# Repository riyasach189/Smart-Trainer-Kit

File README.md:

## Background and Motivation:
- The Digital Trainer Kit serves as a vital tool for facilitating learning, teaching, and testing of digital electronic circuits.
- It plays a crucial role in the laboratory component of the Digital Circuits course offered in Semester 1 at IIIT-D.
- However, the current trainer kits deployed in the ECE labs suffer from drawbacks such as being bulky, expensive, and featuring redundant functions.

## Objectives:
- To find alternatives that are compact, lightweight, and reasonably priced, without compromising essential functionalities.
- To enhance the versatility and functionality of the proposed alternative, a microcontroller will be incorporated into the design. This addition will provide opportunities for future expansion and the inclusion of advanced features, empowering students to explore more complex digital circuits.

## Version 1
**BoM:**
```markdown
| Component                                     | Quantity | Price | Total Cost |
|-----------------------------------------------|----------|-------|------------|
| Arduino Board                                 | 1        | 550   | 550        |
| LEDs                                          | 22       | 0.8   | 17.6       |
| Resistors (330 Ohm)                           | 25       | 0.4   | 10         |
| Push Button Square Switch Self-Locking DPDT   | 10       | 5     | 50         |
| 4511 IC                                       | 1        | 21    | 21         |
| 7 Segment Display (Common Cathode)            | 1        | 7     | 7          |
| Passive Buzzer                                | 1        | 10    | 10         |
| 741 IC                                        | 1        | 9     | 9          |
| 4 mm Banana Sockets                           | 30       | 14.5  | 435        |
|                                               |          |       | 1109.6     |
```

**Features and Description:**
- A 12 V adapter powers the circuit. The Arduino has an inbuilt 12 V to 5 V converter. For the rest of the circuit, a Buck-Boost Converter is used.
- Nested 'for loops' are programmed in the Arduino to provide continuous clock signals of 3 frequencies - 0.1 Hz, 1 Hz, 10 Hz.
- The Continuity Checker can be used to debug faulty connections in a circuit.
- The Voltage Detector returns a HIGH value (LED turns on) when the voltage at a given point exceeds 2.5 V (to accommodate both the CMOS and TTL logic levels) in reference to the circuit ground, and returns a LOW value otherwise. A voltage divider is used between 5 V and GND to set the benchmark voltage at 2.5 V.
- The 4511 IC is connected to a 7-segment display to convert binary input to decimal digits (0 to 9).
- The Input LEDs can be operated using the Push Button switches connected to them.
- There are designated signal detector pins on the Arduino, which can be used to plot the clock signals on the Serial Plotter.

**Problems Encountered:**
- TinkerCad is not a reliable tool for large circuits; not recommended. They have also removed many components from their library.
- Initially, we planned to keep the clock frequencies variable, but Arduino can only run one infinite loop at a time. So, we decided to use nested 'for loops' to provide clock signals.
- We were trying to use a Common Cathode 7 segment display with a 7447 IC before we realized that that IC drives Common Anode displays.
- We found the 7805 IC unstable for voltage conversion, so we switched to a Buck-Boost Converter.
- When we kept the circuit on for a long time, the Input LEDs started flickering when switched ON. This issue remains unresolved. Possible reasons are:
  - The 12 V adapter could not meet the power requirements.
  - Arduino could not meet the power requirements.
  - The plastic and metal holes in the breadboard did not align, leading to loose connections.
  - Poor soldering on Buck-Boost Converter.
- We planned to use toggle switches in the circuit, but they were panel mount instead of PCB mount. So we switched to push button switches.

**Resources:**
- KiCad - PCB Design
- [7 Segment Display with 4511 IC](https://youtu.be/KZTwr95eINc)
- [Arduino for Beginners](https://youtu.be/d8_xXNcGYgo)
- [How to Use DPDT Switches](https://youtu.be/f0EMblUCp54)

## Version 2
**BoM:**
```markdown
| Component                                | Quantity | Price | Total Cost |
|------------------------------------------|----------|-------|------------|
| RPi Pico Board                           | 1        | 345   | 345        |
| LEDs                                     | 18       | 0.8   | 14.4       |
| Resistors (330 Ohm)                      | 24       | 0.4   | 9.6        |
| Toggle switches                          | 10       | 20    | 200        |
| 4511 IC                                  | 1        | 21    | 21         |
| 7 Segment Display (Common Cathode)       | 1        | 7     | 7          |
| DIP Socket (16 Pin)                      | 1        | 3     | 3          |
| ZIF Socket (16 Pin)                      | 1        | 50    | 50         |
| Passive Buzzer                           | 1        | 10    | 10         |
| 2 mm Banana Sockets                      | 30       | 26    | 780        |
| Rotary Encoder                           | 1        | 50    | 50         |
| LCD (16 x 2) + I2C                       | 1        | 188   | 188        |
| 18 mm Standoffs                          | 4        | 16    | 64         |
| Potentiometer                            | 1        | 6     | 6          |
| Female Headers                           | 44       | 1.125 | 49.5       |
|                                          |          |       | 1797.5     |
```

**Features and Description:**
- A 5 V power supply powers the circuit.
- State machines on the rp2040 to provide continuous clock signals of 3 frequencies - 1 Hz, 5 Hz, 10 Hz.
- The Continuity Checker can be used to debug a circuit.
- The 4511 IC is connected to a 7-segment display to convert binary input to decimal digits (0 to 9).
- The Input LEDs can be operated using the toggle switches connected to them.
- The rotary menu is displayed on the LCD screen and operated using the rotary encoder. It has 2 options: IC Tester and Voltmeter.
- If 'Voltmeter' is selected, the LCD displays the voltage (in reference to the circuit GND) at the given point. To exit the voltmeter mode, click on the rotary encoder button.
- To use the IC Tester, plug the IC into the DIP socket (If it's a 14 Pin IC, leave the last 2 pins of the DIP Socket empty, i.e., start from the beginning of the DIP Socket). Then, select which IC you wish to test. The LCD will display '[ ]' for every gate that is functioning and '[!]' for every gate that is not functioning in the IC (keeping the IC notch on the left).

**Problems Encountered:**
- RPi Pico should connect to a Windows system in theory, but we were only able to establish connection in Linux systems.
- To connect an RPi Pico, we require a microUSB to USB cable which supports data and charge transfer, not just charge transfer.
- Pico's LED light did not turn ON the moment it was connected to the power supply, which led us to believe that the Pico was faulty (which is not true).
- It took us some time to decide between using a raw rotary encoder or one mounted on a PCB, due to differences in available online resources. We settled on a PCB-mounted encoder but re-soldered its header pins to be more breadboard-friendly.
- We decided to use an I2C to connect the LCD screen to reduce the number of pins required on RPi Pico. This left extra pins for IC Tester and future expansion.
- RPi Pico is a dual-core processor in theory, but we were unable to use its multithreading functionality. We spent a long time trying to generate clock signals from Pico on the second thread, but Pico could only process one thread at a time. We finally decided to use 555 timers to generate clock signals.
- For the voltmeter, we wanted a range of (0, 5) V but the analog read pins of RPi Pico can take a maximum input of 3.3 V. So we used a voltage divider to map the range (0, 5) V onto (0, 3.3) V, then mapped that back to (0, 5) V in the code.
- We were later able to implement a clock without the use of separate threads through state machines on three different pins; however, having a variable clock was still not possible, and we settled on having three constant clock signals.
- We replaced push button switches with toggle switches because they were shorting the GND and VCC plane in the ON configuration. We believe push button switches are available in 2 different pinouts, but they look the same on the outside, ie. it is not possible to tell from the outside which type of push button switch it is. Also, toggle switches offer more tactile feedback and are a better choice.
- The biggest bottleneck in the whole design process was finding a PCB manufacturer.
- We realised we had missed some traces in the PCB when we assembled the first prototype, so we added them later.
- We had missed the Vcc and GND connection of the 4511 IC, and for some reason, it was causing the IC to heat up whenever we turned the RPi Pico on. This problem was resolved when we provided Vcc and GND to the IC.

**Resources:**
- [Rotary Encoder with RPi Pico](https://youtu.be/sgnEUxeNxpM)
- [RPi Pico for Beginners](https://youtu.be/1WDagiA8fdU)
- [Connect LCD to RPi Pico using I2C](https://www.tomshardware.com/how-to/lcd-display-raspberry-pi-pico)
- [555 Timer IC in Astable Mode](https://youtu.be/iJYm_BGqa1A)
- [555 Timer Frequency Calculator in Astable Mode](https://ohmslawcalculator.com/555-astable-calculator)
- [State Machines on RPi Pico](https://www.ourpcb.com/programmable-io.html)
  
## Contributors:
- Dr. Rahul Gupta - Manager, Research Labs (Supervisor of the Project)
- [Riya Sachdeva - EVE, BTech 2026](https://github.com/riyasach189)
- [Surat Sathi Samanta - EVE, BTech 2026](https://github.com/kio42069/)
- [Aarav Mathur - CSSS, BTech 2026](https://github.com/13100d/)

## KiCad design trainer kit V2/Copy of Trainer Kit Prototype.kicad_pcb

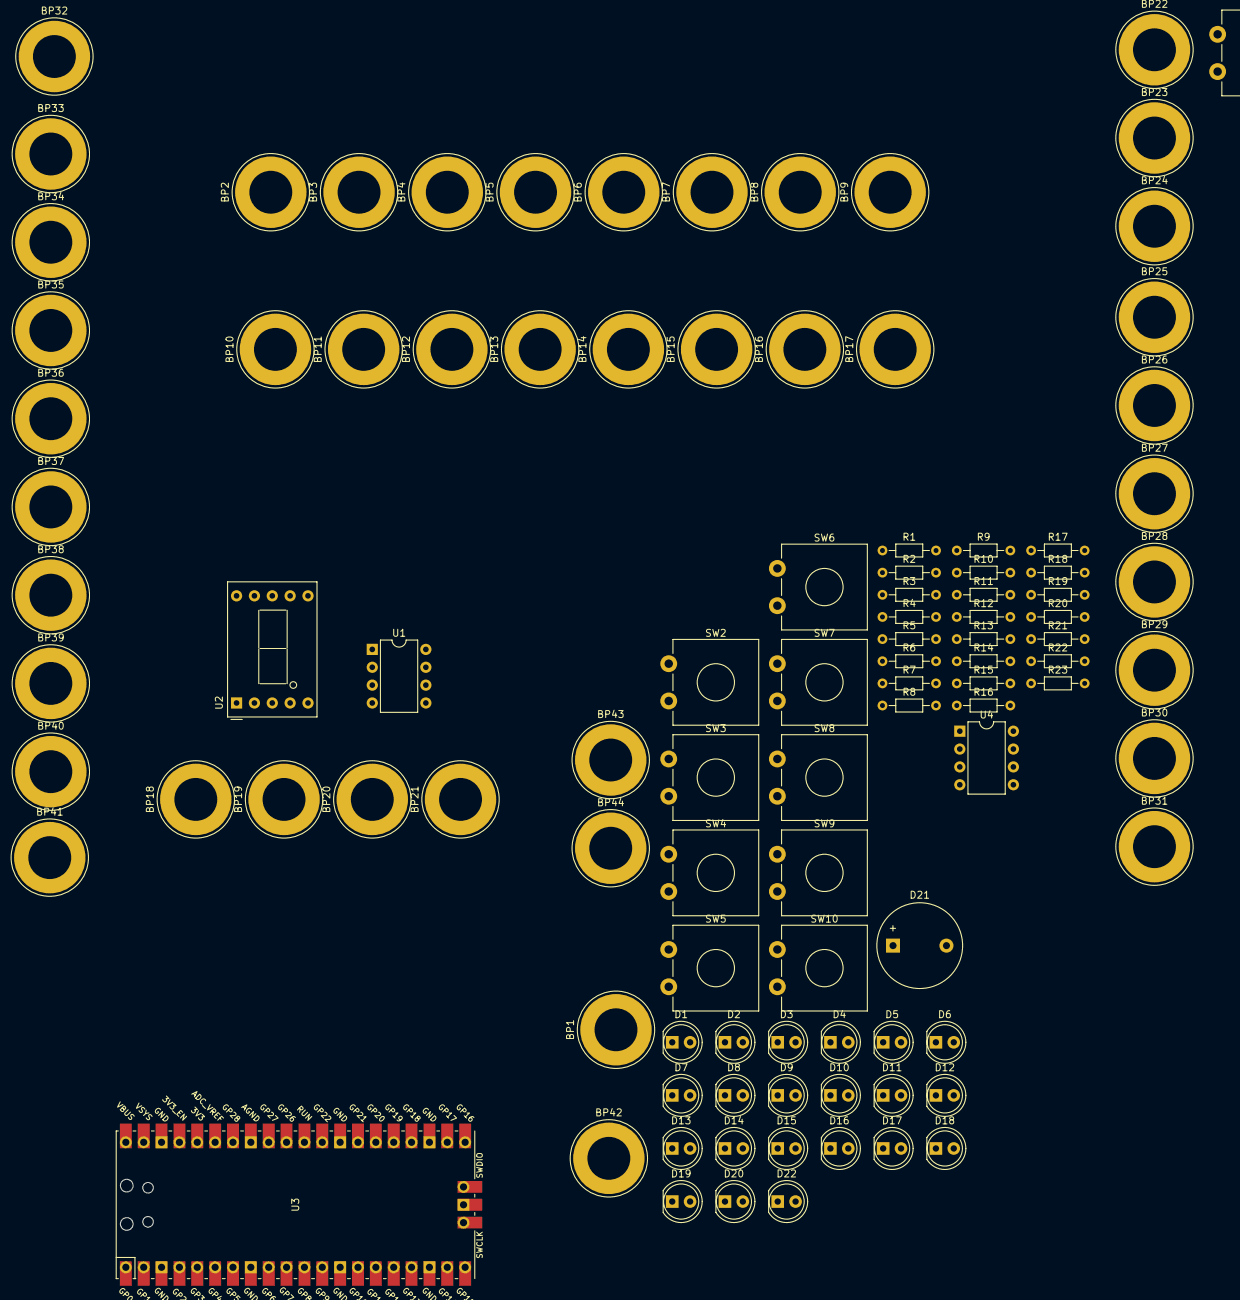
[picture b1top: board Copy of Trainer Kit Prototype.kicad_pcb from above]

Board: 2 copper layers, 103 parts (0 on the bottom side), 69 nets, no tracks yet.

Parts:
BP1, BP2, BP3, BP4, BP5, BP6, BP7, BP8, BP9, BP10, BP11, BP12, BP13, BP14, BP15, BP16, BP17, BP18, BP19, BP20, BP21, BP22, BP23, BP24, BP25, BP26, BP27, BP28, BP29, BP30, BP31, BP32, BP33, BP34, BP35, BP36, BP37, BP38, BP39, BP40, BP41, BP42, BP43, BP44: banana plug; Banana_Jack_1Pin
D1, D2, D3, D4, D5, D6, D7, D8, D9, D10, D11, D12, D13, D14, D15, D16, D17, D18, D19, D20: CQY99; LED_D5.0mm_IRGrey
D21: LED; Buzzer_12x9.5RM7.6
D22: LED; LED_D5.0mm_IRGrey
R1, R2, R3, R4, R5, R6, R7, R8, R9, R10, R11, R12, R13, R14, R15, R16, R17, R18, R19, R20, R21, R22, R23: 330; R_Axial_DIN0204_L3.6mm_D1.6mm_P7.62mm_Horizontal
SW1, SW2, SW3, SW4, SW5, SW6, SW7, SW8, SW9, SW10: SW_DIP_x01; SW_CW_GPTS203211B
U1: CD4511B; DIP-8_W7.62mm
U2: D168K; D1X8K
U3: Pico; RPi_Pico_SMD_TH
U4: LM741; DIP-8_W7.62mm

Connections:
+5V: BP44.1 (A), R23.2, SW1.1, SW2.1, SW3.1, SW4.1, SW5.1, SW6.1, SW7.1, SW8.1, SW9.1, SW10.1, U4.7 (V+)
/V(input): BP42.1 (A), U4.3 (+)
/Voltmeter Input Line: BP1.1 (A), U3.4 (GPIO2)
/automated testing (output lines): BP14.1 (A), U3.25 (GPIO19)
GNDREF: D21.2 (A), R1.1, R2.1, R3.1, R4.1, R5.1, R6.1, R7.1, R8.1, R9.1, R10.1, R11.1, R12.1, R13.1, R14.1, R15.1, R16.1, R17.1, R18.1, R19.1, R20.1, R21.1, R22.1, U1.5 (~EL), U2.3 (CC), U2.8 (CC), U3.8 (GND), U4.4 (V-)
unnamed: BP2.1 (A), U3.11 (GPIO8)
unnamed: BP3.1 (A), U3.12 (GPIO9)
unnamed: BP4.1 (A), U3.14 (GPIO10)
unnamed: BP5.1 (A), U3.15 (GPIO11)
unnamed: BP6.1 (A), U3.16 (GPIO12)
unnamed: BP7.1 (A), U3.17 (GPIO13)
unnamed: BP8.1 (A), U3.19 (GPIO14)
unnamed: BP9.1 (A), U3.20 (GPIO15)
unnamed: BP10.1 (A), U3.31 (GPIO26_ADC0)
unnamed: BP11.1 (A), U3.29 (GPIO22)
unnamed: BP12.1 (A), U3.27 (GPIO21)
unnamed: BP13.1 (A), U3.26 (GPIO20)
unnamed: BP15.1 (A), U3.24 (GPIO18)
unnamed: BP16.1 (A), U3.22 (GPIO17)
unnamed: BP17.1 (A), U3.21 (GPIO16)
unnamed: BP18.1 (A), U1.7 (DA)
unnamed: BP19.1 (A), U1.1 (DB)
unnamed: BP20.1 (A), U1.2 (DC)
unnamed: BP21.1 (A), U1.6 (DD)
unnamed: BP22.1 (A), D11.2 (A)
unnamed: BP23.1 (A), D12.2 (A)
unnamed: BP24.1 (A), D13.2 (A)
unnamed: BP25.1 (A), D14.2 (A)
unnamed: BP26.1 (A), D15.2 (A)
unnamed: BP27.1 (A), D16.2 (A)
unnamed: BP28.1 (A), D17.2 (A)
unnamed: BP29.1 (A), D18.2 (A)
unnamed: BP30.1 (A), D19.2 (A)
unnamed: BP31.1 (A), D20.2 (A)
unnamed: BP32.1 (A), D1.2 (A), SW9.2
unnamed: BP33.1 (A), D2.2 (A), SW8.2
unnamed: BP34.1 (A), D3.2 (A), SW7.2
unnamed: BP35.1 (A), D4.2 (A), SW1.2
unnamed: BP36.1 (A), D5.2 (A), SW2.2
unnamed: BP37.1 (A), D6.2 (A), SW3.2
unnamed: BP38.1 (A), D7.2 (A), SW4.2
unnamed: BP39.1 (A), D8.2 (A), SW5.2
unnamed: BP40.1 (A), D9.2 (A), SW6.2
unnamed: BP41.1 (A), D10.2 (A), SW10.2
unnamed: BP43.1 (A), D21.1 (K)
unnamed: D1.1 (K), R1.2
unnamed: D2.1 (K), R2.2
unnamed: D3.1 (K), R3.2
unnamed: D4.1 (K), R4.2
unnamed: D5.1 (K), R5.2
unnamed: D6.1 (K), R6.2
unnamed: D7.1 (K), R7.2
unnamed: D8.1 (K), R8.2
unnamed: D9.1 (K), R9.2
unnamed: D10.1 (K), R10.2
unnamed: D11.1 (K), R11.2
unnamed: D12.1 (K), R12.2
unnamed: D13.1 (K), R13.2
unnamed: D14.1 (K), R14.2
unnamed: D15.1 (K), R15.2
unnamed: D16.1 (K), R16.2
unnamed: D17.1 (K), R17.2
unnamed: D18.1 (K), R18.2
unnamed: D19.1 (K), R19.2
unnamed: D20.1 (K), R20.2
unnamed: D22.2 (A), U4.6
unnamed: D22.1 (K), R21.2
unnamed: R22.2, R23.1, U4.2 (-)
VDD: U1.3 (~LT), U1.4 (~BI)

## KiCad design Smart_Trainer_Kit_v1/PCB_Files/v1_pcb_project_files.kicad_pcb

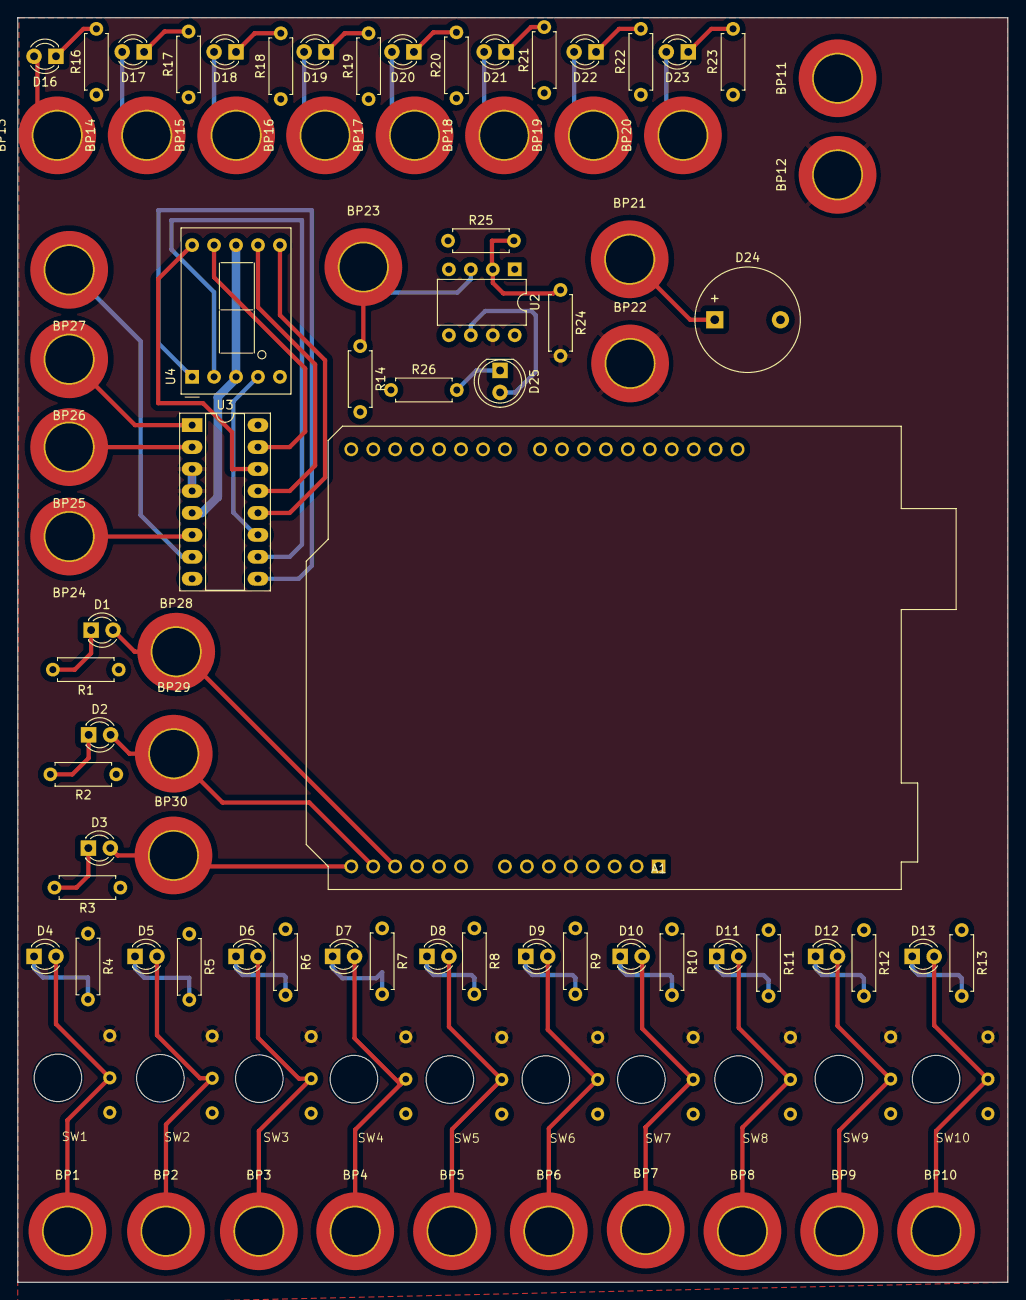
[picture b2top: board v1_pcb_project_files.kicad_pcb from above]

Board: 2 copper layers, 114.5 x 146.3 mm, 92 parts (0 on the bottom side), 60 nets.

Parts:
A1: Arduino_UNO_R3
BP1, BP2, BP3, BP4, BP5, BP6, BP7, BP8, BP9, BP10, BP11, BP12, BP13, BP14, BP15, BP16, BP17, BP18, BP19, BP20, BP21, BP22, BP23, BP24, BP25, BP26, BP27, BP28, BP29, BP30: banana plug; banana_plug(modified thickness)
D1, D2, D3, D4, D5, D6, D7, D8, D9, D10, D11, D12, D13, D16, D17, D18, D19, D20, D21, D22, D23: CQY99; LED_D3.0mm
D24: LED; Buzzer_12x9.5RM7.6
D25: LED; LED_D5.0mm_IRGrey
R1, R2, R3, R4, R5, R6, R7, R8, R9, R10, R11, R12, R13, R14, R16, R17, R18, R19, R20, R21, R22, R23, R24, R25, R26: 330; R_Axial_DIN0207_L6.3mm_D2.5mm_P7.62mm_Horizontal
SW1, SW2, SW3, SW4, SW5, SW6, SW7, SW8, SW9, SW10: SW_Push_SPDT; SPDT_platemount_switch(platemount)
U2: LM741; DIP-8_W7.62mm
U3: CD4511B; DIP-16_W7.62mm_Socket_LongPads
U4: D168K; D1X8K

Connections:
+5V: A1.5 (+5V), BP12.1 (A), BP22.1 (A), R24.2, SW1.1 (A), SW2.1 (A), SW3.1 (A), SW4.1 (A), SW5.1 (A), SW6.1 (A), SW7.1 (A), SW8.1 (A), SW9.1 (A), SW10.1 (A), U2.7 (V+), U3.3 (~LT), U3.4 (~BI)
/V(input): BP23.1 (A), R14.1, U2.3 (+)
GNDREF: A1.29 (GND), BP11.1 (A), D24.2 (A), R1.1, R2.1, R3.1, R4.1, R5.1, R6.1, R7.1, R8.1, R9.1, R10.1, R11.1, R12.1, R13.1, R14.2, R16.1, R17.1, R18.1, R19.1, R20.1, R21.1, R22.1, R23.1, R25.1, R26.1, SW1.3 (C), SW2.3 (C), SW3.3 (C), SW4.3 (C), SW5.3 (C), SW6.3 (C), SW7.3 (C), SW8.3 (C), SW9.3 (C), SW10.3 (C), U2.4 (V-), U3.5 (~EL), U4.3 (CC), U4.8 (CC)
unnamed: A1.12 (A3), BP28.1 (A), D1.2 (A)
unnamed: BP1.1 (A), D4.2 (A), SW1.2 (B)
unnamed: BP2.1 (A), D5.2 (A), SW2.2 (B)
unnamed: BP3.1 (A), D6.2 (A), SW3.2 (B)
unnamed: BP4.1 (A), D7.2 (A), SW4.2 (B)
unnamed: BP5.1 (A), D8.2 (A), SW5.2 (B)
unnamed: BP6.1 (A), D9.2 (A), SW6.2 (B)
unnamed: BP7.1 (A), D10.2 (A), SW7.2 (B)
unnamed: BP8.1 (A), D11.2 (A), SW8.2 (B)
unnamed: BP9.1 (A), D12.2 (A), SW9.2 (B)
unnamed: BP10.1 (A), D13.2 (A), SW10.2 (B)
unnamed: BP13.1 (A), D16.2 (A)
unnamed: BP14.1 (A), D17.2 (A)
unnamed: BP15.1 (A), D18.2 (A)
unnamed: BP16.1 (A), D19.2 (A)
unnamed: BP17.1 (A), D20.2 (A)
unnamed: BP18.1 (A), D21.2 (A)
unnamed: BP19.1 (A), D22.2 (A)
unnamed: BP20.1 (A), D23.2 (A)
unnamed: BP21.1 (A), D24.1 (K)
unnamed: BP24.1 (A), U3.6 (DD)
unnamed: BP25.1 (A), U3.2 (DC)
unnamed: BP26.1 (A), U3.1 (DB)
unnamed: BP27.1 (A), U3.7 (DA)
unnamed: A1.13 (SDA/A4), BP29.1 (A), D2.2 (A)
unnamed: A1.14 (SCL/A5), BP30.1 (A), D3.2 (A)
unnamed: D1.1 (K), R1.2
unnamed: D2.1 (K), R2.2
unnamed: D3.1 (K), R3.2
unnamed: D4.1 (K), R4.2
unnamed: D5.1 (K), R5.2
unnamed: D6.1 (K), R6.2
unnamed: D7.1 (K), R7.2
unnamed: D8.1 (K), R8.2
unnamed: D9.1 (K), R9.2
unnamed: D10.1 (K), R10.2
unnamed: D11.1 (K), R11.2
unnamed: D12.1 (K), R12.2
unnamed: D13.1 (K), R13.2
unnamed: D16.1 (K), R16.2
unnamed: D17.1 (K), R17.2
unnamed: D18.1 (K), R18.2
unnamed: D19.1 (K), R19.2
unnamed: D20.1 (K), R20.2
unnamed: D21.1 (K), R21.2
unnamed: D22.1 (K), R22.2
unnamed: D23.1 (K), R23.2
unnamed: D25.2 (A), U2.6
unnamed: D25.1 (K), R26.2
unnamed: R24.1, R25.2, U2.2 (-)
unnamed: U3.13 (Qa), U4.7 (A)
unnamed: U3.12 (Qb), U4.6 (B)
unnamed: U3.11 (Qc), U4.4 (C)
unnamed: U3.10 (Qd), U4.2 (D)
unnamed: U3.9 (Qe), U4.1 (E)
unnamed: U3.15 (Qf), U4.9 (F)
unnamed: U3.14 (Qg), U4.10 (G)

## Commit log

2023-07-06 Added gate testing codes for basic gates, left : d flip flop, 4x1 mux and 2x1 mux
2023-07-06 added return statements
2023-07-06 added code for mux 1
2023-07-06 jijijijij
2023-07-06 restarted, im a fucken dumbass
2023-07-06 the aarav commit
2023-07-07 Create v2_without_clock
2023-07-07 Create rotary_menu
2023-07-07 Create rotary_encoder_sample
2023-07-07 Create rotary_encoder_main
2023-07-07 Create rotary_encoder_classes
2023-07-07 Create voltmeter
2023-07-07 aalas
2023-07-07 development done, needs ic testing now
2023-07-07 use IC name to call funtion now
2023-07-07 sorry
2023-07-07 done
2023-07-24 smart trainer kit v2 final code
2023-07-24 cleaned uo
2023-07-24 cleaned up
2023-07-24 added necessary codes
2023-08-11 Update README.md
    update for latest design iteration
2023-08-19 Update constants.py
    fix mux testcases ( B,A select line assumption caused bug ).
2023-08-29 Update boot.py
    quality of life improvement fucking power led
2023-12-29 pcb files
2024-01-02 Update constants.py
    shuffle gpio allocation ( make path routing for pcb easier )
